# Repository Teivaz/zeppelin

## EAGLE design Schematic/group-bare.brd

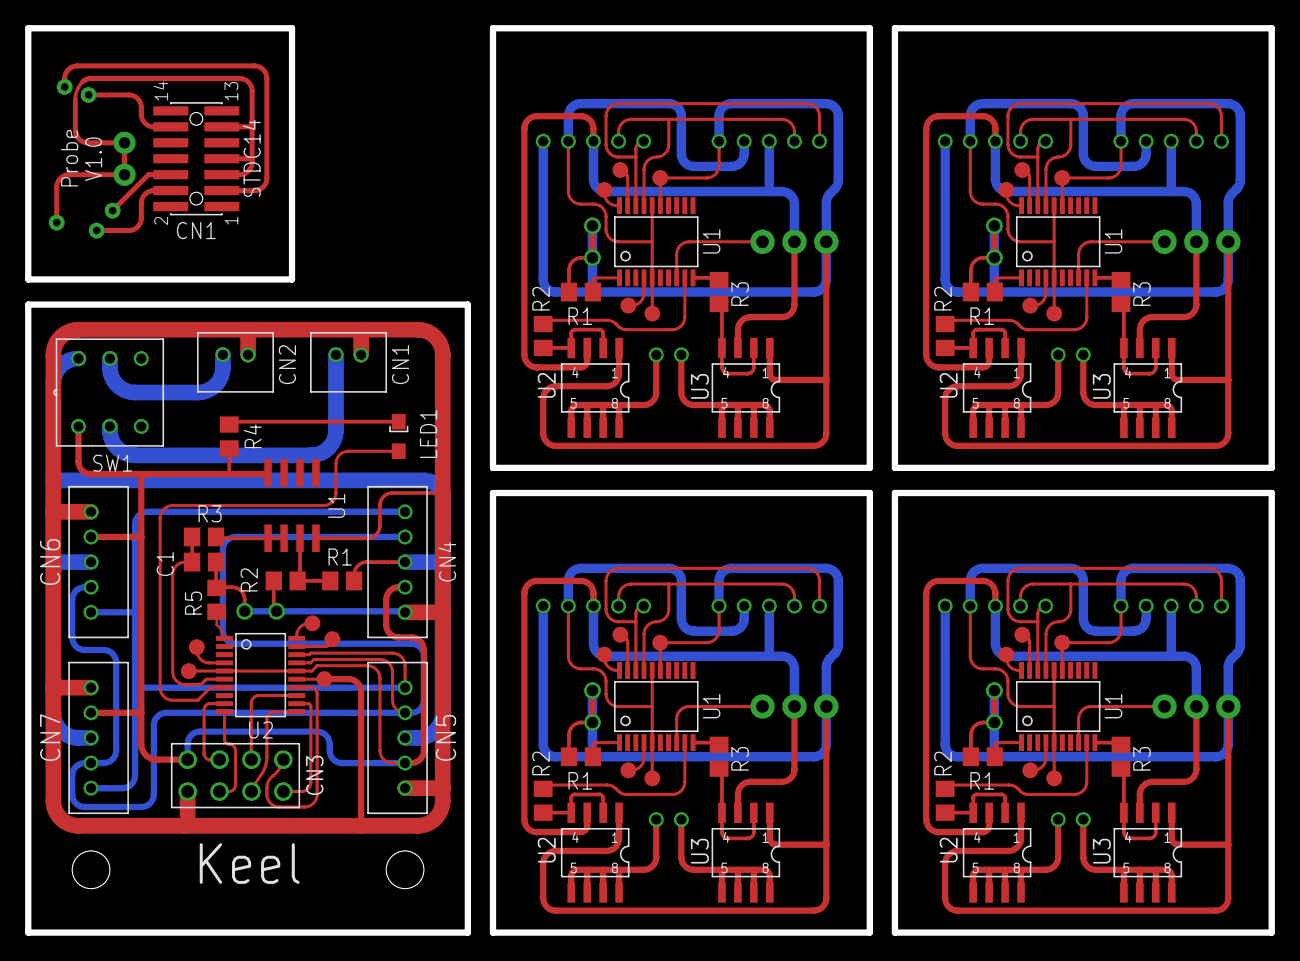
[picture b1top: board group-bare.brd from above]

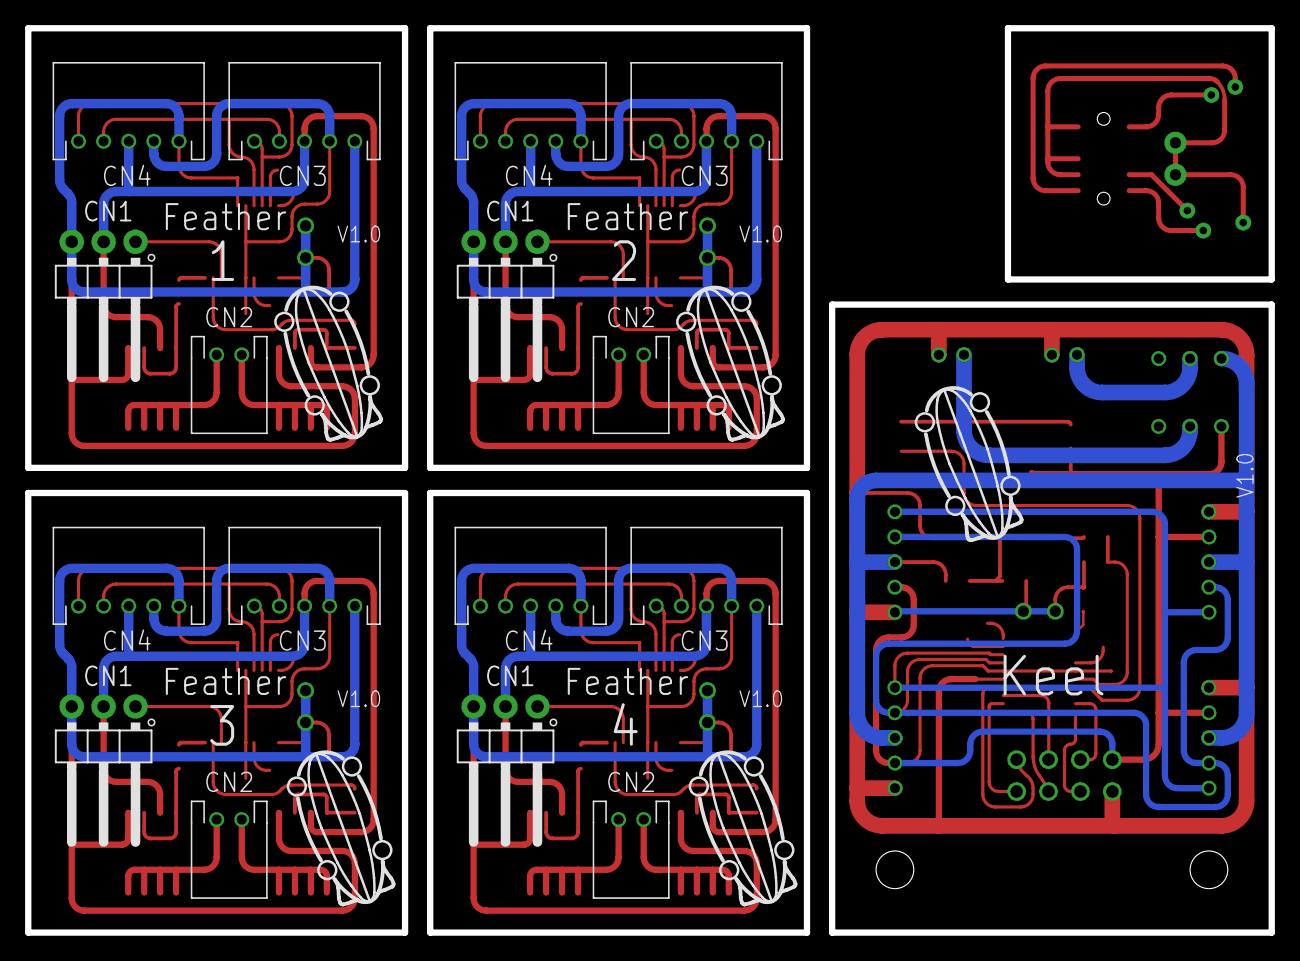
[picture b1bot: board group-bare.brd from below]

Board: 2 copper layers, 99.0 x 72.0 mm, 69 parts (21 on the bottom side), 91 nets.

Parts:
C1: 470pf; C0805
CN0, CN10, CN15, CN20, CN25: KEEL_PROBE1IC; KEEL_PROBE-IC1
CN1: STDC14; FTSH-107-01-L-DV-K-A
CN2: KEEL_PROBE1PROBE; KEEL_PROBE1
CN3: BAT0; 1X2
CN4: BAT1; 1X2
CN5: NRF24013; PIN
CN6: F1; 1X5
CN7: F2; 1X5
CN8: F3; 1X5
CN9: F4; 1X5
CN11, CN16, CN21, CN26: 1X2HORIZONTAL; 1X2H
CN12, CN14, CN17, CN19, CN22, CN24, CN27, CN29: F1; 1X5H
CN13, CN18, CN23, CN28: 1X03/90
E$1, E$2, E$3, E$4, E$5: ZEPPELIN
LED1: AP2012
R1, R2: 10k; R0805
R3: 500r; R0805
R4: 300r; R0805
R5, R8, R11, R14, R17: 1k; R0805
R6, R7, R9, R10, R12, R13, R15, R16: 51k; R0805
SW1: TL2201
U1: LM358D; SO08
U2, U5, U8, U11, U14: STM32L011; SSOP20
U3, U4, U6, U7, U9, U10, U12, U13: IRF7105; SO8-2

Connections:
+3V1: CN12.3, CN13.2, CN14.3, U3.3, U4.3
+3V2: CN17.3, CN18.2, CN19.3, U6.3, U7.3
+3V3: CN6.3, CN7.3, CN8.3, CN9.3, R1.2, SW1.4
+3V4: CN22.3, CN23.2, CN24.3, U9.3, U10.3
+3V5: CN27.3, CN28.2, CN29.3, U12.3, U13.3
GND: CN1.05, CN1.07, CN1.11, CN2.GND, CN2.GND-D1, CN2.GND-D2
GND1: C1.1, CN0.GND, CN0.GND-D1, CN0.GND-D2, CN3.2, CN4.2, CN5.1, CN6.1, CN7.1, CN8.1, CN9.1, R2.1, R5.1, U1.4, U2.15
GND2: CN10.GND, CN10.GND-D1, CN10.GND-D2, CN12.1, CN13.3, CN14.1, R8.1, U3.1, U4.1, U5.15
GND3: CN15.GND, CN15.GND-D1, CN15.GND-D2, CN17.1, CN18.3, CN19.1, R11.1, U6.1, U7.1, U8.15
GND4: CN20.GND, CN20.GND-D1, CN20.GND-D2, CN22.1, CN23.3, CN24.1, R14.1, U9.1, U10.1, U11.15
GND5: CN25.GND, CN25.GND-D1, CN25.GND-D2, CN27.1, CN28.3, CN29.1, R17.1, U12.1, U13.1, U14.15
I2C_SCL: CN6.4, CN7.4, CN8.4, CN9.4, U2.17
I2C_SCL1: CN12.4, CN14.4, U5.17
I2C_SCL2: CN17.4, CN19.4, U8.17
I2C_SCL3: CN22.4, CN24.4, U11.17
I2C_SCL4: CN27.4, CN29.4, U14.17
I2C_SDA: CN6.5, CN7.5, CN8.5, CN9.5, U2.18
I2C_SDA1: CN12.5, CN14.5, U5.18
I2C_SDA2: CN17.5, CN19.5, U8.18
I2C_SDA3: CN22.5, CN24.5, U11.18
I2C_SDA4: CN27.5, CN29.5, U14.18
unnamed: R1.1, R2.2, U1.3
unnamed: LED1.C, R4.2
unnamed: LED1.A, U2.7
unnamed: C1.2, R3.1, U2.6
unnamed: R5.2, U2.1
unnamed: R3.2, U1.1, U1.2
unnamed: CN4.1, SW1.5
unnamed: CN3.1, SW1.2
unnamed: CN11.2, U3.5, U3.6, U3.7, U3.8
unnamed: CN11.1, U4.5, U4.6, U4.7, U4.8
unnamed: R6.1, U3.2, U3.4
unnamed: R7.2, U4.2, U4.4
unnamed: R8.2, U5.1
unnamed: R7.1, U5.10
unnamed: R6.2, U5.9
unnamed: CN13.1, U5.8
unnamed: CN16.2, U6.5, U6.6, U6.7, U6.8
unnamed: CN16.1, U7.5, U7.6, U7.7, U7.8
unnamed: R9.1, U6.2, U6.4
unnamed: R10.2, U7.2, U7.4
unnamed: R11.2, U8.1
unnamed: R10.1, U8.10
unnamed: R9.2, U8.9
unnamed: CN18.1, U8.8
unnamed: CN21.2, U9.5, U9.6, U9.7, U9.8
unnamed: CN21.1, U10.5, U10.6, U10.7, U10.8
unnamed: R12.1, U9.2, U9.4
unnamed: R13.2, U10.2, U10.4
unnamed: R14.2, U11.1
unnamed: R13.1, U11.10
unnamed: R12.2, U11.9
unnamed: CN23.1, U11.8
unnamed: CN26.2, U12.5, U12.6, U12.7, U12.8
unnamed: CN26.1, U13.5, U13.6, U13.7, U13.8
unnamed: R15.1, U12.2, U12.4
unnamed: R16.2, U13.2, U13.4
unnamed: R17.2, U14.1
unnamed: R16.1, U14.10
unnamed: R15.2, U14.9
unnamed: CN28.1, U14.8
NRST: CN1.12, CN2.NRST
NRST1: CN0.NRST, U2.4
NRST2: CN10.NRST, U5.4
NRST3: CN15.NRST, U8.4
NRST4: CN20.NRST, U11.4
NRST5: CN25.NRST, U14.4
SPI_CE: CN5.3, U2.10
SPI_CSN: CN5.4, U2.9
SPI_IRQ: CN5.8, U2.14
SPI_MISO: CN5.7, U2.12
SPI_MOSI: CN5.6, U2.13
SPI_SCK: CN5.5, U2.11
SWCLK: CN1.06, CN2.CLK
SWCLK1: CN0.CLK, U2.20
SWCLK2: CN10.CLK, U5.20
SWCLK3: CN15.CLK, U8.20
SWCLK4: CN20.CLK, U11.20
SWCLK5: CN25.CLK, U14.20
SWDIO: CN1.04, CN2.DIO
SWDIO1: CN0.DIO, U2.19
SWDIO2: CN10.DIO, U5.19
SWDIO3: CN15.DIO, U8.19
SWDIO4: CN20.DIO, U11.19
SWDIO5: CN25.DIO, U14.19
T_VCC: CN1.03, CN2.VCC
VCC: CN0.VCC, CN5.2, CN6.2, CN7.2, CN8.2, CN9.2, R4.1, SW1.1, U1.8, U2.5, U2.16
VCC1: CN10.VCC, CN12.2, CN14.2, U5.5, U5.16
VCC2: CN15.VCC, CN17.2, CN19.2, U8.5, U8.16
VCC3: CN20.VCC, CN22.2, CN24.2, U11.5, U11.16
VCC4: CN25.VCC, CN27.2, CN29.2, U14.5, U14.16

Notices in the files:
parts and their libraries:
irf-2: Copyright & License
This library is licensed under the General Public License, Version 2.
More Information about the General Public License is available at http://www.gnu.org/copyleft/gpl.html.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
